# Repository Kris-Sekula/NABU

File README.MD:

I will keep stuff related to NABU here

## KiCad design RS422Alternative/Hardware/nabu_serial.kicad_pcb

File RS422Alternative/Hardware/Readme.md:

Created some PCBs for the USB adaptor, sources are in KiCad 6.0

This adapter "intercepts" the RX  and TX signals that originally go to the RS422 circuit and "injects" the RX,TX from the USB to serial adapter... There is also option to "inject" alternative clock signal (as suggested by one of my viewers)...this should allow a real 115200 bps speeds.

Components used:
* PCB: you can use the sources to generate the gerbers or simply order from [PCBWay](https://www.pcbway.com/project/shareproject/NABU_native_USB_to_serial_adapter_4c1e523b.html)
* 2x 20pin gold round pin headers, example [eBay](https://www.ebay.com/itm/391866775529)
* DIP40 socket, example - select 40pin ones [Aliexpress](https://www.aliexpress.us/item/2255800861848499.html?)
* USB-to-TTL serial adapter, example [Aliexpress](https://www.aliexpress.us/item/3256804658745564.html?)
* (optional) 1.8432MHz Oscillator module, example [Digikey](https://www.digikey.com/en/products/detail/ecs-inc/ECS-2100A-018/21259)

Installed in NABU

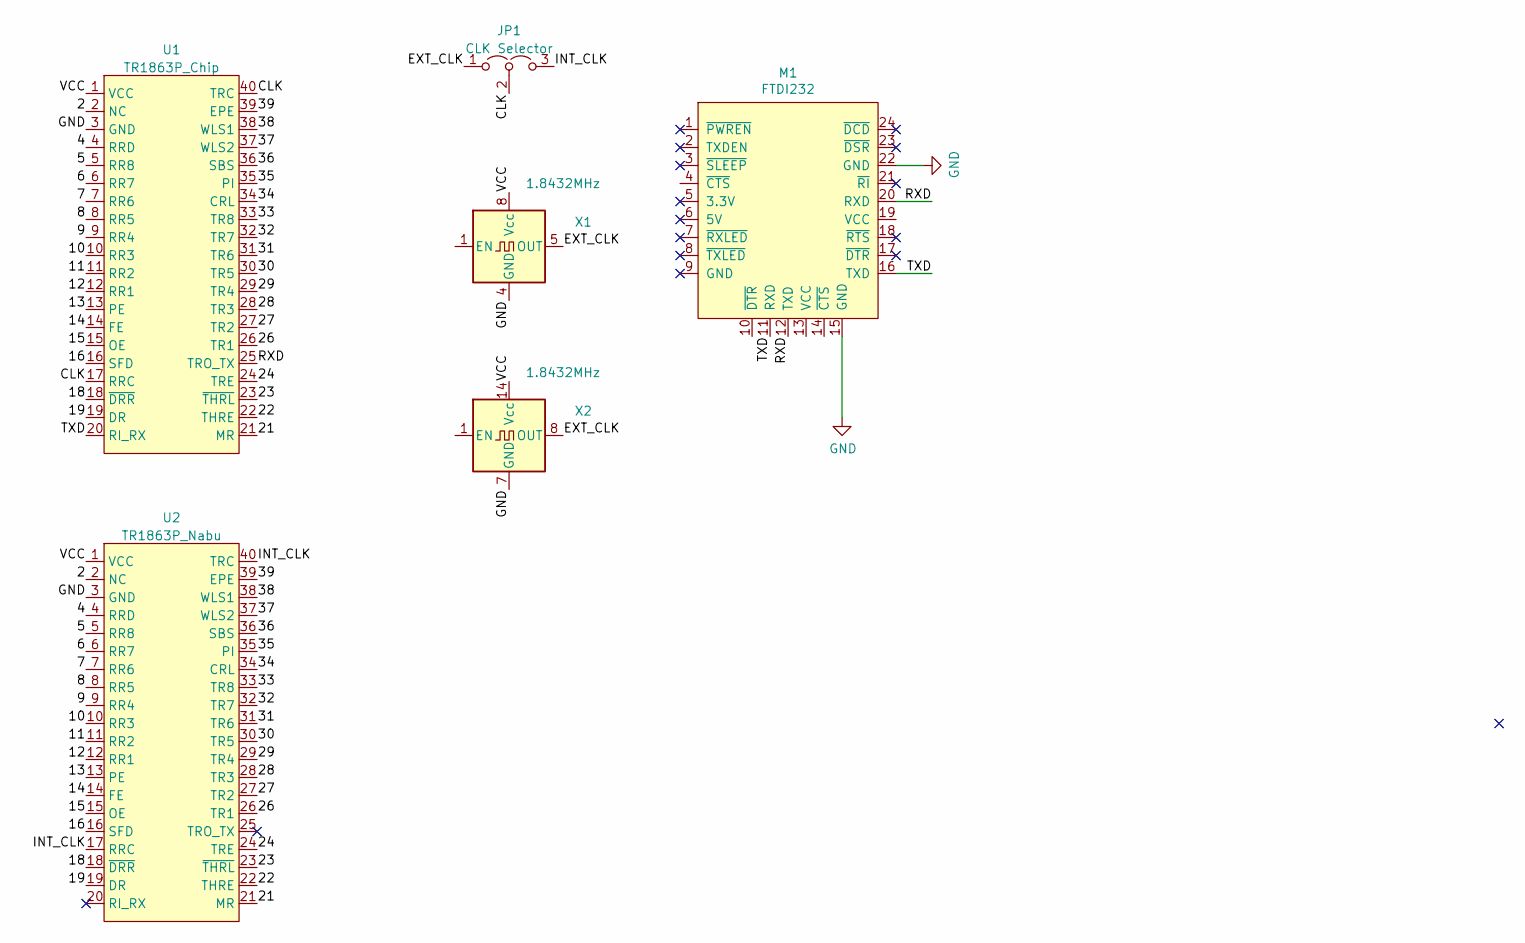
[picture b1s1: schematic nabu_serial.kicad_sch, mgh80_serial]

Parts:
JP1: CLK Selector; SolderJumper-3_P2.0mm_Open_TrianglePad1.0x1.5mm
M1: FTDI232; FTDI232_Full
U1: TR1863P_Chip; DIP-40_W15.24mm_Socket
U2: TR1863P_Nabu; DIP-40_W15.24mm_Socket
X1: 1.8432MHz; Oscillator_DIP-8
X2: 1.8432MHz; Oscillator_DIP-14

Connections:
/2: U1.2 (NC), U2.2 (NC)
/4: U1.4 (RRD), U2.4 (RRD)
/5: U1.5 (RR8), U2.5 (RR8)
/6: U1.6 (RR7), U2.6 (RR7)
/7: U1.7 (RR6), U2.7 (RR6)
/8: U1.8 (RR5), U2.8 (RR5)
/9: U1.9 (RR4), U2.9 (RR4)
/10: U1.10 (RR3), U2.10 (RR3)
/11: U1.11 (RR2), U2.11 (RR2)
/12: U1.12 (RR1), U2.12 (RR1)
/13: U1.13 (PE), U2.13 (PE)
/14: U1.14 (FE), U2.14 (FE)
/15: U1.15 (OE), U2.15 (OE)
/16: U1.16 (SFD), U2.16 (SFD)
/18: U1.18 (~DRR), U2.18 (~DRR)
/19: U1.19 (DR), U2.19 (DR)
/21: U1.21 (MR), U2.21 (MR)
/22: U1.22 (THRE), U2.22 (THRE)
/23: U1.23 (~THRL), U2.23 (~THRL)
/24: U1.24 (TRE), U2.24 (TRE)
/26: U1.26 (TR1), U2.26 (TR1)
/27: U1.27 (TR2), U2.27 (TR2)
/28: U1.28 (TR3), U2.28 (TR3)
/29: U1.29 (TR4), U2.29 (TR4)
/30: U1.30 (TR5), U2.30 (TR5)
/31: U1.31 (TR6), U2.31 (TR6)
/32: U1.32 (TR7), U2.32 (TR7)
/33: U1.33 (TR8), U2.33 (TR8)
/34: U1.34 (CRL), U2.34 (CRL)
/35: U1.35 (PI), U2.35 (PI)
/36: U1.36 (SBS), U2.36 (SBS)
/37: U1.37 (WLS2), U2.37 (WLS2)
/38: U1.38 (WLS1), U2.38 (WLS1)
/39: U1.39 (EPE), U2.39 (EPE)
/CLK: JP1.2 (C), U1.17 (RRC), U1.40 (TRC)
/EXT_CLK: JP1.1 (A), X1.5 (OUT), X2.8 (OUT)
/INT_CLK: JP1.3 (B), U2.17 (RRC), U2.40 (TRC)
/RXD: M1.12 (TXD), M1.20 (RXD), U1.25 (TRO_TX)
/TXD: M1.11 (RXD), M1.16 (TXD), U1.20 (RI_RX)
/VCC: U1.1 (VCC), U2.1 (VCC), X1.8 (Vcc), X2.14 (Vcc)
GND: M1.15 (GND), M1.22 (GND), U1.3 (GND), U2.3 (GND), X1.4 (GND), X2.7 (GND)

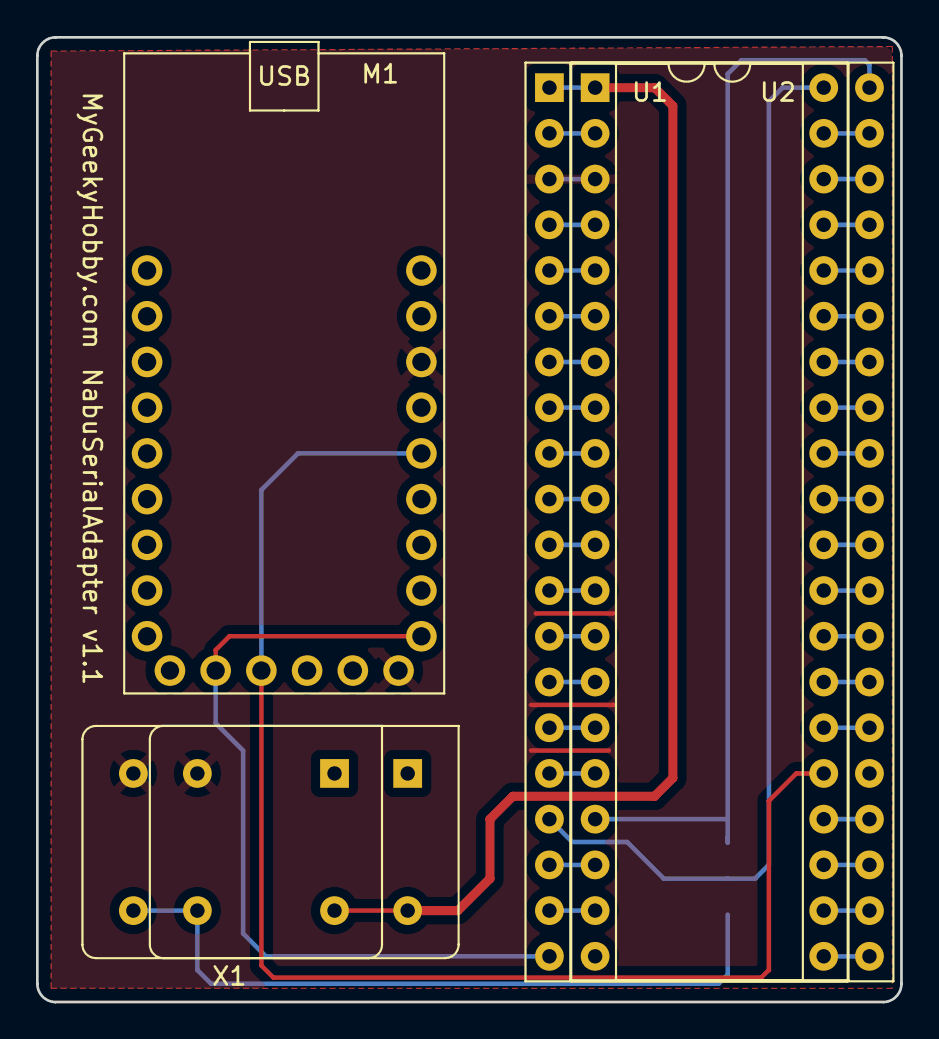
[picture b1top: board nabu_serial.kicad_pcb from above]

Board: 2 copper layers, 48.0 x 53.6 mm, 6 parts (1 on the bottom side), 41 nets.

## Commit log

2022-12-05 Files used with EPROM Emulator
2022-12-07 Added Serial interface diagram
2022-12-07 It works
2022-12-10 Added ESP8266 in action
2022-12-31 Added PDF schematic
2022-12-31 Updated BOM
2023-01-01 KiCad sources added
